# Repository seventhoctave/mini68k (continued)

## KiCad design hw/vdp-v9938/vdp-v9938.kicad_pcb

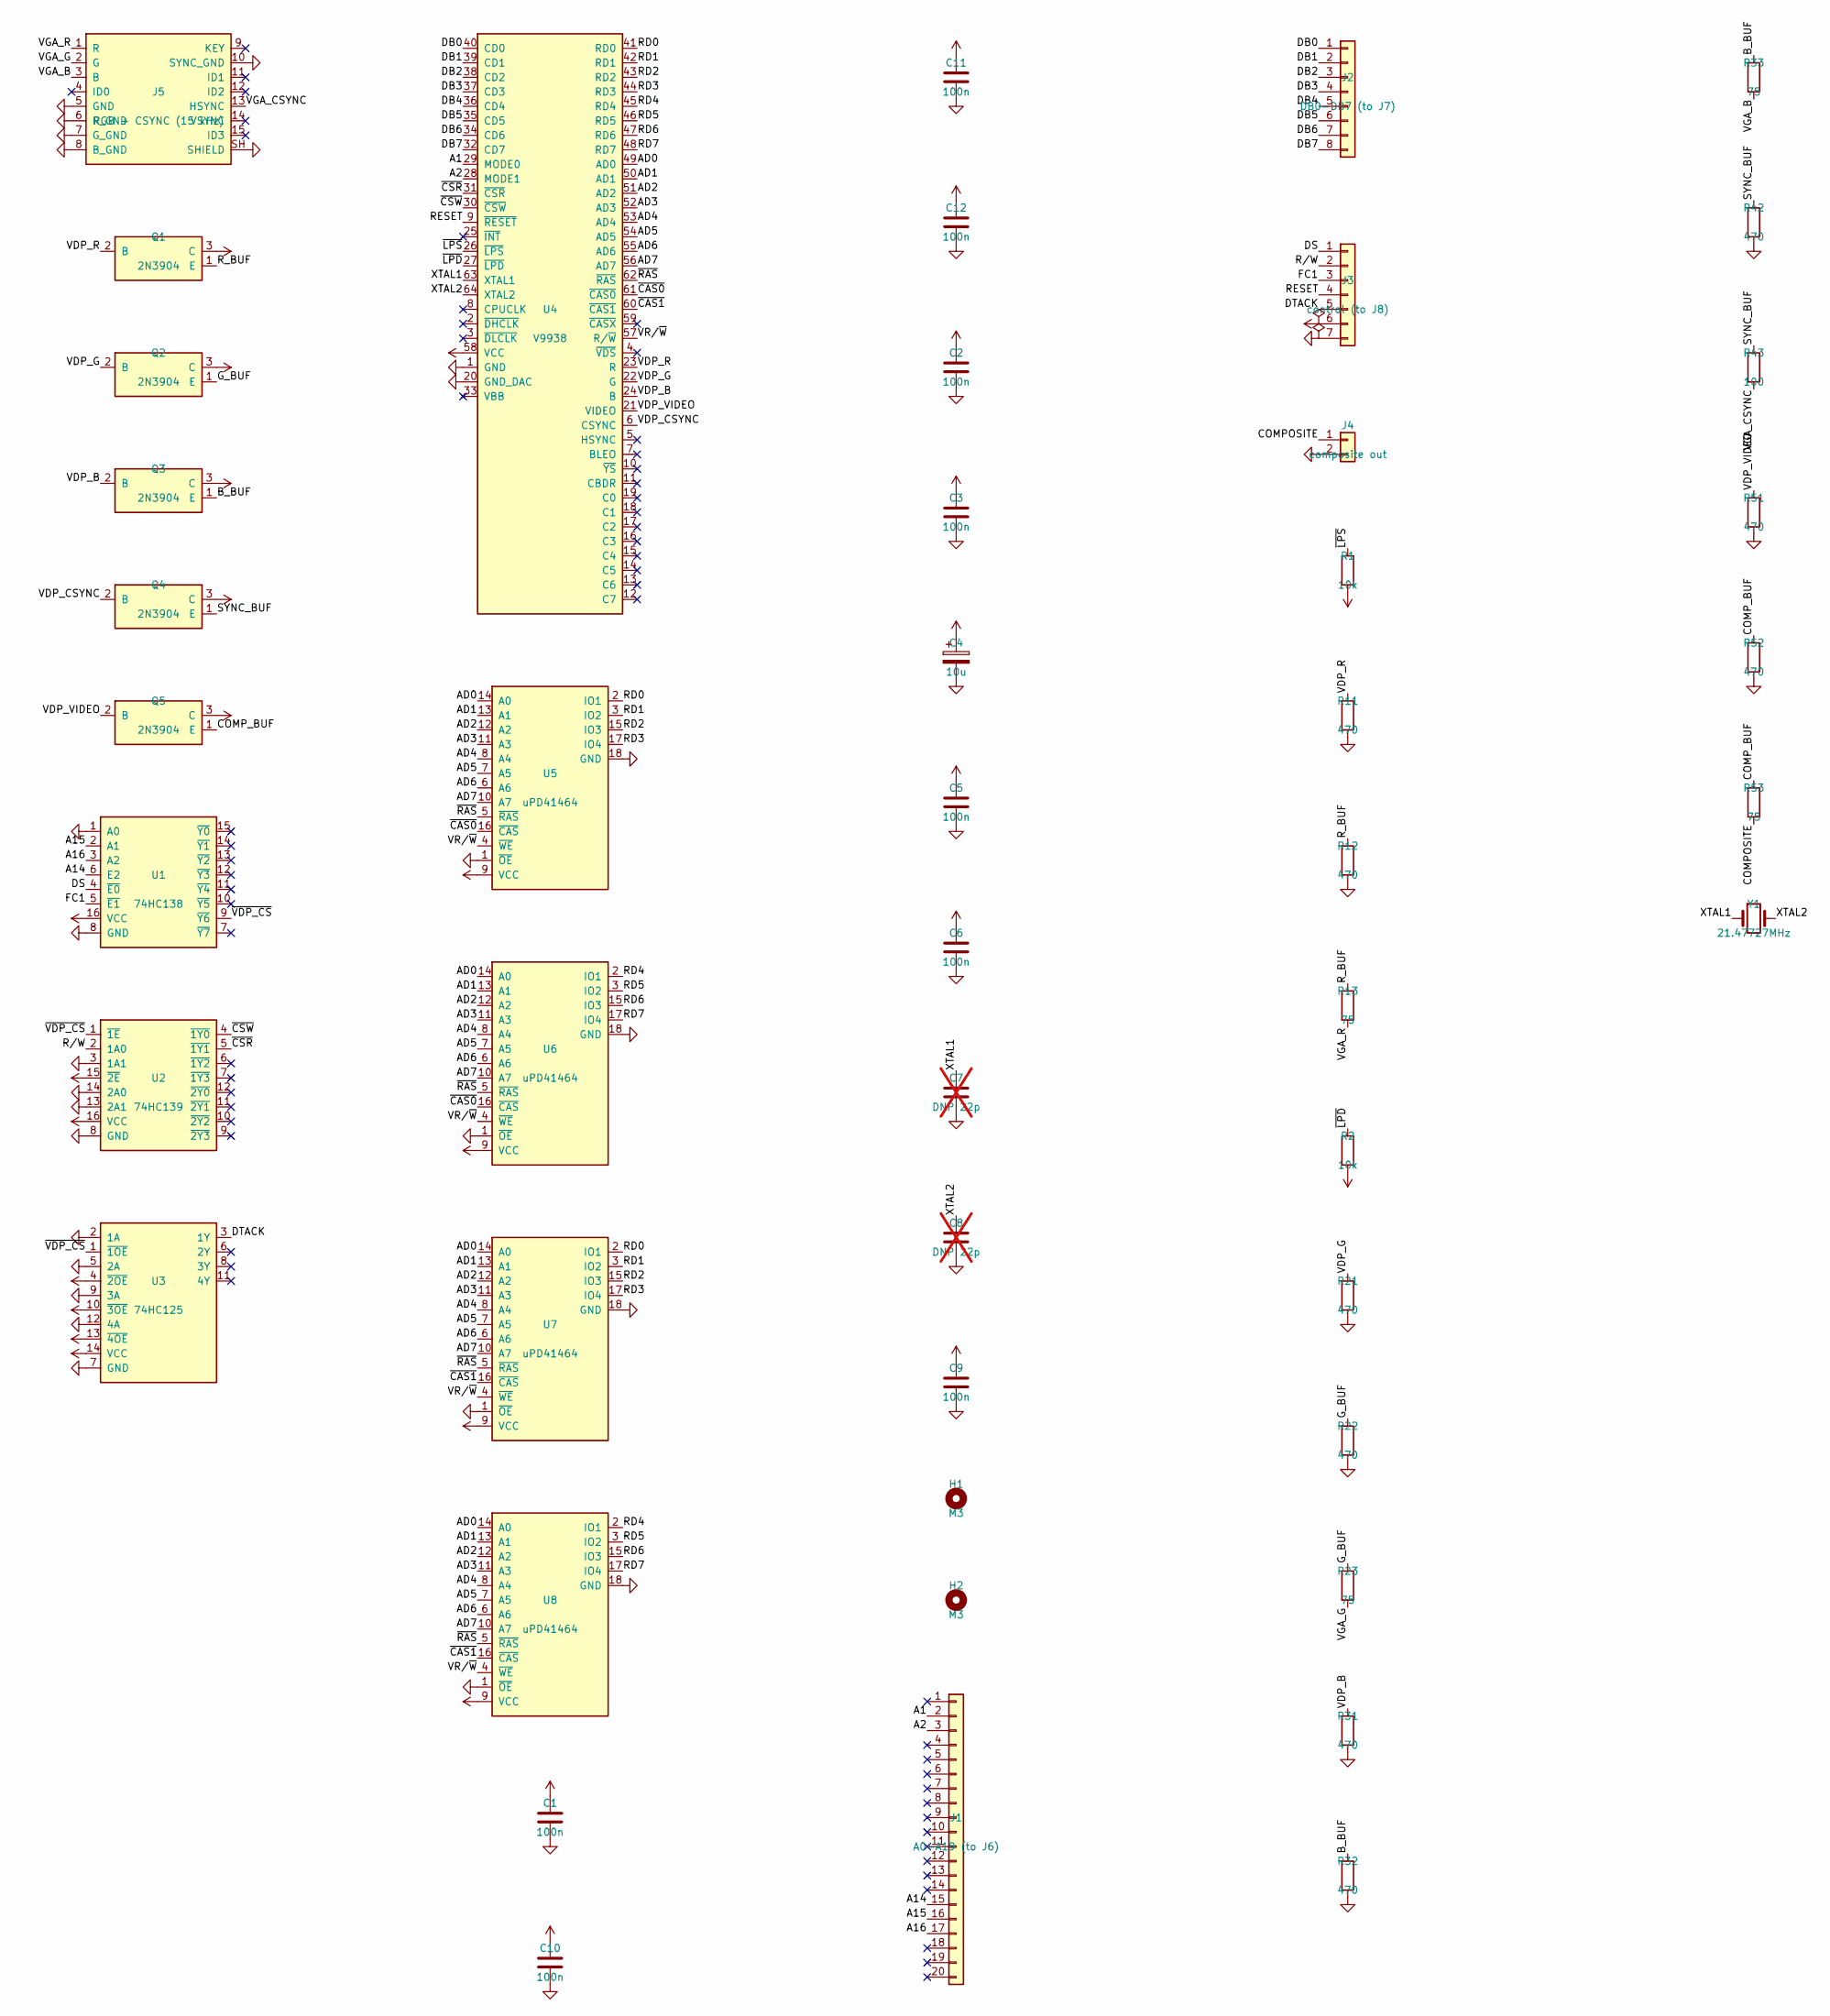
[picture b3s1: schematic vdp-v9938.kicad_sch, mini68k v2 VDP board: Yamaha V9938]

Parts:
C1, C2, C3, C5, C6, C9, C10, C11, C12: 100n; C_Disc_D5.0mm_W2.5mm_P2.50mm
C4: 10u; CP_Radial_D5.0mm_P2.50mm
C7, C8: DNP 22p; C_Disc_D5.0mm_W2.5mm_P2.50mm; not fitted
H1, H2: M3; MountingHole_3.2mm_M3
J1: A0-A19 (to J6); PinSocket_1x20_P2.54mm_Horizontal
J2: DB0-DB7 (to J7); PinSocket_1x08_P2.54mm_Horizontal
J3: control (to J8); PinSocket_1x07_P2.54mm_Horizontal
J4: composite out; PinHeader_1x02_P2.54mm_Vertical
J5: RGB + CSYNC (15 kHz); DSUB-15-HD_Socket_Horizontal_P2.29x1.90mm_EdgePinOffset3.03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
Q1, Q2, Q3, Q4, Q5: 2N3904; TO-92_Inline_Wide
R1, R2: 10k; R_Axial_DIN0207_L6.3mm_D2.5mm_P7.62mm_Horizontal
R11, R12, R21, R22, R31, R32, R42, R51, R52: 470; R_Axial_DIN0207_L6.3mm_D2.5mm_P7.62mm_Horizontal
R13, R23, R33, R53: 75; R_Axial_DIN0207_L6.3mm_D2.5mm_P7.62mm_Horizontal
R43: 100; R_Axial_DIN0207_L6.3mm_D2.5mm_P7.62mm_Horizontal
U1: 74HC138; DIP-16_W7.62mm_LongPads
U2: 74HC139; DIP-16_W7.62mm_LongPads
U3: 74HC125; DIP-14_W7.62mm_LongPads
U4: V9938; SDIP-64_W19.05mm_P1.778mm
U5, U6, U7, U8: uPD41464; DIP-18_W7.62mm_LongPads
Y1: 21.47727MHz; Crystal_HC49-4H_Vertical

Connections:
/A1: J1.2, U4.29 (MODE0)
/A2: J1.3, U4.28 (MODE1)
/A14: J1.15, U1.6 (E2)
/A15: J1.16, U1.2 (A1)
/A16: J1.17, U1.3 (A2)
/AD0: U4.49 (AD0), U5.14 (A0), U6.14 (A0), U7.14 (A0), U8.14 (A0)
/AD1: U4.50 (AD1), U5.13 (A1), U6.13 (A1), U7.13 (A1), U8.13 (A1)
/AD2: U4.51 (AD2), U5.12 (A2), U6.12 (A2), U7.12 (A2), U8.12 (A2)
/AD3: U4.52 (AD3), U5.11 (A3), U6.11 (A3), U7.11 (A3), U8.11 (A3)
/AD4: U4.53 (AD4), U5.8 (A4), U6.8 (A4), U7.8 (A4), U8.8 (A4)
/AD5: U4.54 (AD5), U5.7 (A5), U6.7 (A5), U7.7 (A5), U8.7 (A5)
/AD6: U4.55 (AD6), U5.6 (A6), U6.6 (A6), U7.6 (A6), U8.6 (A6)
/AD7: U4.56 (AD7), U5.10 (A7), U6.10 (A7), U7.10 (A7), U8.10 (A7)
/B_BUF: Q3.1 (E), R32.1, R33.1
/COMPOSITE: J4.1, R53.2
/COMP_BUF: Q5.1 (E), R52.1, R53.1
/DB0: J2.1, U4.40 (CD0)
/DB1: J2.2, U4.39 (CD1)
/DB2: J2.3, U4.38 (CD2)
/DB3: J2.4, U4.37 (CD3)
/DB4: J2.5, U4.36 (CD4)
/DB5: J2.6, U4.35 (CD5)
/DB6: J2.7, U4.34 (CD6)
/DB7: J2.8, U4.32 (CD7)
/DS: J3.1, U1.4 (~E0)
/DTACK: J3.5, U3.3 (1Y)
/FC1: J3.3, U1.5 (~E1)
/G_BUF: Q2.1 (E), R22.1, R23.1
/RD0: U4.41 (RD0), U5.2 (IO1), U7.2 (IO1)
/RD1: U4.42 (RD1), U5.3 (IO2), U7.3 (IO2)
/RD2: U4.43 (RD2), U5.15 (IO3), U7.15 (IO3)
/RD3: U4.44 (RD3), U5.17 (IO4), U7.17 (IO4)
/RD4: U4.45 (RD4), U6.2 (IO1), U8.2 (IO1)
/RD5: U4.46 (RD5), U6.3 (IO2), U8.3 (IO2)
/RD6: U4.47 (RD6), U6.15 (IO3), U8.15 (IO3)
/RD7: U4.48 (RD7), U6.17 (IO4), U8.17 (IO4)
/RESET: J3.4, U4.9 (~RESET)
/R_BUF: Q1.1 (E), R12.1, R13.1
/R/W: J3.2, U2.2 (1A0)
/SYNC_BUF: Q4.1 (E), R42.1, R43.1
/VDP_B: Q3.2 (B), R31.1, U4.24 (B)
/VDP_CSYNC: Q4.2 (B), U4.6 (CSYNC)
/VDP_G: Q2.2 (B), R21.1, U4.22 (G)
/VDP_R: Q1.2 (B), R11.1, U4.23 (R)
/VDP_VIDEO: Q5.2 (B), R51.1, U4.21 (VIDEO)
/VGA_B: J5.3 (B), R33.2
/VGA_CSYNC: J5.13 (HSYNC), R43.2
/VGA_G: J5.2 (G), R23.2
/VGA_R: J5.1 (R), R13.2
/VR/~W: U4.57 (R/~W), U5.4 (~WE), U6.4 (~WE), U7.4 (~WE), U8.4 (~WE)
/XTAL1: C7.1, U4.63 (XTAL1), Y1.1
/XTAL2: C8.1, U4.64 (XTAL2), Y1.2
/~CAS0: U4.61 (~CAS0), U5.16 (~CAS), U6.16 (~CAS)
/~CAS1: U4.60 (~CAS1), U7.16 (~CAS), U8.16 (~CAS)
/~CSR: U2.5 (~1Y1), U4.31 (~CSR)
/~CSW: U2.4 (~1Y0), U4.30 (~CSW)
/~LPD: R2.1, U4.27 (~LPD)
/~LPS: R1.1, U4.26 (~LPS)
/~RAS: U4.62 (~RAS), U5.5 (~RAS), U6.5 (~RAS), U7.5 (~RAS), U8.5 (~RAS)
/~VDP_CS: U1.9 (~Y6), U2.1 (~1E), U3.1 (~1OE)
GND: C1.2, C2.2, C3.2, C4.2, C5.2, C6.2, C7.2, C8.2, C9.2, C10.2, C11.2, C12.2, J3.7, J4.2, J5.5 (GND), J5.6 (R_GND), J5.7 (G_GND), J5.8 (B_GND), J5.10 (SYNC_GND), J5.SH (SHIELD), R11.2, R12.2, R21.2, R22.2, R31.2, R32.2, R42.2, R51.2, R52.2, U1.1 (A0), U1.8 (GND), U2.3 (1A1), U2.8 (GND), U2.13 (2A1), U2.14 (2A0), U3.2 (1A), U3.5 (2A), U3.7 (GND), U3.9 (3A), U3.12 (4A), U4.1 (GND), U4.20 (GND_DAC), U5.1 (~OE), U5.18 (GND), U6.1 (~OE), U6.18 (GND), U7.1 (~OE), U7.18 (GND), U8.1 (~OE), U8.18 (GND)
VCC: C1.1, C2.1, C3.1, C4.1, C5.1, C6.1, C9.1, C10.1, C11.1, C12.1, J3.6, Q1.3 (C), Q2.3 (C), Q3.3 (C), Q4.3 (C), Q5.3 (C), R1.2, R2.2, U1.16 (VCC), U2.15 (~2E), U2.16 (VCC), U3.4 (~2OE), U3.10 (~3OE), U3.13 (~4OE), U3.14 (VCC), U4.58 (VCC), U5.9 (VCC), U6.9 (VCC), U7.9 (VCC), U8.9 (VCC)

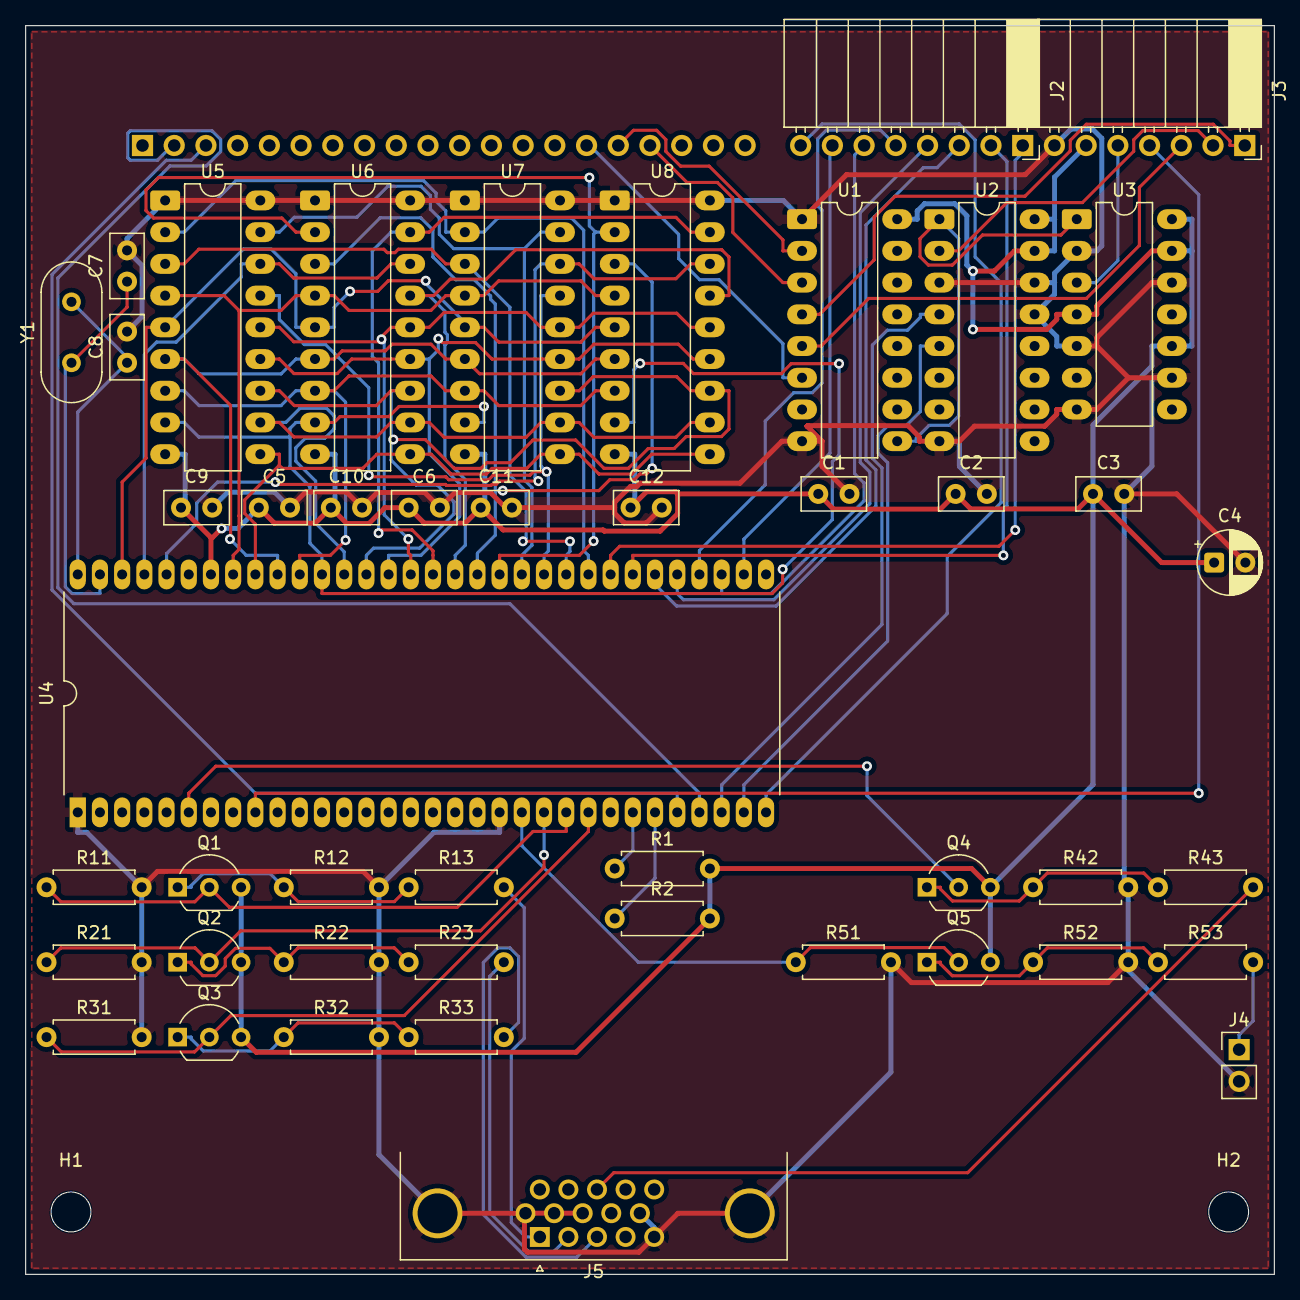
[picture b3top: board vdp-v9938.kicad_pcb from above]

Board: 2 copper layers, 100.0 x 100.0 mm, 49 parts (1 on the bottom side), 62 nets.

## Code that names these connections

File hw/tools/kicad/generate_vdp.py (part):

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     pins('40:CD0:b,39:CD1:b,38:CD2:b,37:CD3:b,36:CD4:b,35:CD5:b,34:CD6:b,32:CD7:b,29:MODE0:i,28:MODE1:i,'
          '31:~{CSR}:i,30:~{CSW}:i,9:~{RESET}:i,25:~{INT}:oc,26:~{LPS}:i,27:~{LPD}:i,63:XTAL1:i,64:XTAL2:p,'
          '8:CPUCLK:o,2:~{DHCLK}:oc,3:~{DLCLK}:oc,58:VCC:pw,1:GND:pw,20:GND_DAC:pw,33:VBB:nc'),
     pins('41:RD0:b,42:RD1:b,43:RD2:b,44:RD3:b,45:RD4:b,46:RD5:b,47:RD6:b,48:RD7:b,49:AD0:o,50:AD1:o,51:AD2:o,'
          '52:AD3:o,53:AD4:o,54:AD5:o,55:AD6:o,56:AD7:o,62:~{RAS}:o,61:~{CAS0}:o,60:~{CAS1}:o,59:~{CASX}:o,'
          '57:R/~{W}:o,4:~{VDS}:o,23:R:o,22:G:o,24:B:o,21:VIDEO:o,6:CSYNC:b,5:HSYNC:b,7:BLEO:oc,10:~{YS}:o,'
          '11:CBDR:o,19:C0:b,18:C1:b,17:C2:b,16:C3:b,15:C4:b,14:C5:b,13:C6:b,12:C7:b')),
    ('TMS9918A', 'U', 'Package_DIP:DIP-40_W15.24mm_LongPads',
     'TI TMS9918A VDP (data manual 3.7.1). CD0/AD0/RD0 are the MSBs',
     pins('24:CD0:b,23:CD1:b,22:CD2:b,21:CD3:b,20:CD4:b,19:CD5:b,18:CD6:b,17:CD7:b,13:MODE:i,15:~{CSR}:i,'
          '14:~{CSW}:i,34:~{RESET}/SYNC:i,16:~{INT}:o,40:XTAL1:i,39:XTAL2:p,38:CPUCLK:o,37:GROMCLK:o,'
          '33:VCC:pw,12:VSS:pw'),
     pins('32:RD0:i,31:RD1:i,30:RD2:i,29:RD3:i,28:RD4:i,27:RD5:i,26:RD6:i,25:RD7:i,10:AD0:o,9:AD1:o,8:AD2:o,'
          '7:AD3:o,6:AD4:o,5:AD5:o,4:AD6:o,3:AD7:o,1:~{RAS}:o,2:~{CAS}:o,11:R/~{W}:o,36:COMVID:o,35:EXTVDP:i')),
    ('uPD41464', 'U', 'Package_DIP:DIP-18_W7.62mm_LongPads',
     'NEC uPD41464 64K x 4 DRAM, 18-pin DIP (NEC data sheet 3B-1)',
     pins('14:A0:i,13:A1:i,12:A2:i,11:A3:i,8:A4:i,7:A5:i,6:A6:i,10:A7:i,5:~{RAS}:i,16:~{CAS}:i,4:~{WE}:i,'
          '1:~{OE}:i,9:VCC:pw'),
     pins('2:IO1:b,3:IO2:b,15:IO3:b,17:IO4:b,18:GND:pw')),
    ('4164', 'U', 'Package_DIP:DIP-16_W7.62mm_LongPads',
     '64K x 1 DRAM, +5 V single supply (4116 signal pinout, pin 9 = A7)',
     pins('5:A0:i,7:A1:i,6:A2:i,12:A3:i,11:A4:i,10:A5:i,13:A6:i,9:A7:i,4:~{RAS}:i,15:~{CAS}:i,3:~{W}:i,'
          '8:VCC:pw,1:NC:nc'),
     pins('2:D:i,14:Q:t,16:VSS:pw')),
    ('74HC138', 'U', 'Package_DIP:DIP-16_W7.62mm_LongPads', '3-to-8 line decoder',
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    ps.append(part('U1', 'vdp:74HC138', '74HC138', None,
                   {'1': 'GND', '2': 'A15', '3': 'A16', '6': 'A14', '4': 'DS', '5': 'FC1', '9': '~{VDP_CS}',
                    '16': 'VCC', '8': 'GND'}, (151.0, 185.5, 0, 'F')))
    # /CSW when R/W = 0, /CSR when R/W = 1
    ps.append(part('U2', 'vdp:74HC139', '74HC139', None,
                   {'1': '~{VDP_CS}', '2': 'R{slash}W', '3': 'GND', '4': '~{CSW}', '5': '~{CSR}',
                    '15': 'VCC', '14': 'GND', '13': 'GND', '16': 'VCC', '8': 'GND'}, (162.0, 185.5, 0, 'F')))
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    ps += emitter_follower(4, 'VDP_CSYNC', 'SYNC_BUF', 'VGA_CSYNC', 150.5, 239.0, series='100')
    ps += emitter_follower(5, 'VDP_VIDEO', 'COMP_BUF', 'COMPOSITE', 150.5, 245.0, load='470')
    ps.append(part('J4', 'Connector_Generic:Conn_01x02', 'composite out',
                   'Connector_PinHeader_2.54mm:PinHeader_1x02_P2.54mm_Vertical', {'1': 'COMPOSITE', '2': 'GND'},
                   (186.0, 252.0, 0, 'F')))
    ps.append(part('J5', 'vdp:DE15_HD', 'RGB + CSYNC (15 kHz)', None,
                   {'1': 'VGA_R', '2': 'VGA_G', '3': 'VGA_B', '5': 'GND', '6': 'GND', '7': 'GND', '8': 'GND',
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           '33': 'VCC', '12': 'GND', '1': '~{RAS}', '2': '~{CAS}', '11': 'VR{slash}~{W}', '36': 'COMVID',
           '35': 'EXTVDP'}
    for k in range(8):
        vdp[str(32 - k)] = 'RD%d' % k       # RD0 pin 32 ... RD7 pin 25
        vdp[str(10 - k)] = 'AD%d' % k       # AD0 pin 10 ... AD7 pin 3
    # rot 90: pins 1-20 run left->right along y=207, pins 40->21 along y=191.76
    ps.append(part('U4', 'vdp:TMS9918A', 'TMS9918A', None, vdp, (92.0, 207.0, 90, 'F')))
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    # Composite: 330R pull-down on the source-follower output (manual fig. 3-3), then a buffer
    ps += emitter_follower(1, 'COMVID', 'COMP_BUF', 'COMPOSITE', 100.0, 260.5, load='330')
    ps.append(part('J4', 'Connector_Generic:Conn_01x02', 'composite out',
                   'Connector_PinHeader_2.54mm:PinHeader_1x02_P2.54mm_Vertical', {'1': 'COMPOSITE', '2': 'GND'},
                   (150.0, 259.2, 0, 'F')))
    for i, (x, y) in enumerate(((92.7, 266.0), (185.4, 266.0))):
        ps.append(part('H%d' % (i + 1), 'Mechanical:MountingHole', 'M3', HOLE, {}, (x, y, 0, 'F')))
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
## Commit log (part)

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2018-06-12 "port" of Mike Christle's mini68k bios to gasm
2018-06-12 URL to original
2018-06-13 print hex, dump mem, fill mem
2018-06-13 bug in parsing params for dump mem
2018-06-14 add line feed to strings
2018-06-19 * intial checkin of kicad schematics
2018-06-20 * oscillator, gal
2018-06-20 everything but reset and i/o
2018-06-20 picture of breadboard version
2018-06-22 initial pcb layout
2018-06-22 initial layout
2018-06-22 routing complete
2018-06-23 3d model
2018-06-23 re-pour planes
2018-06-28 v2 fixes:
    - swapped rx/tx
    - reset switch
    - pullup RST
    - pin one of X1
    - remove VCC plane from under 7805
2019-03-03 gal pld
2019-03-10 KiCad 5
2019-03-10 update footprints, expose i/o from 68681
2019-03-11 run drc and fix issues
2019-03-11 better fills
2019-03-11 more updated footprints and 3d
2019-03-11 better 3d
2019-03-13 jumpers for 27256/28256
2019-03-13 labels
2019-03-15 update symbols
2019-03-15 correct ram pinout... update symbols
2019-03-15 galasm format pld
2019-03-17 seperate crystal for DUART
2019-03-17 v1 pcb photo
2019-09-25 backup
2020-07-29 100x100 pcb image
